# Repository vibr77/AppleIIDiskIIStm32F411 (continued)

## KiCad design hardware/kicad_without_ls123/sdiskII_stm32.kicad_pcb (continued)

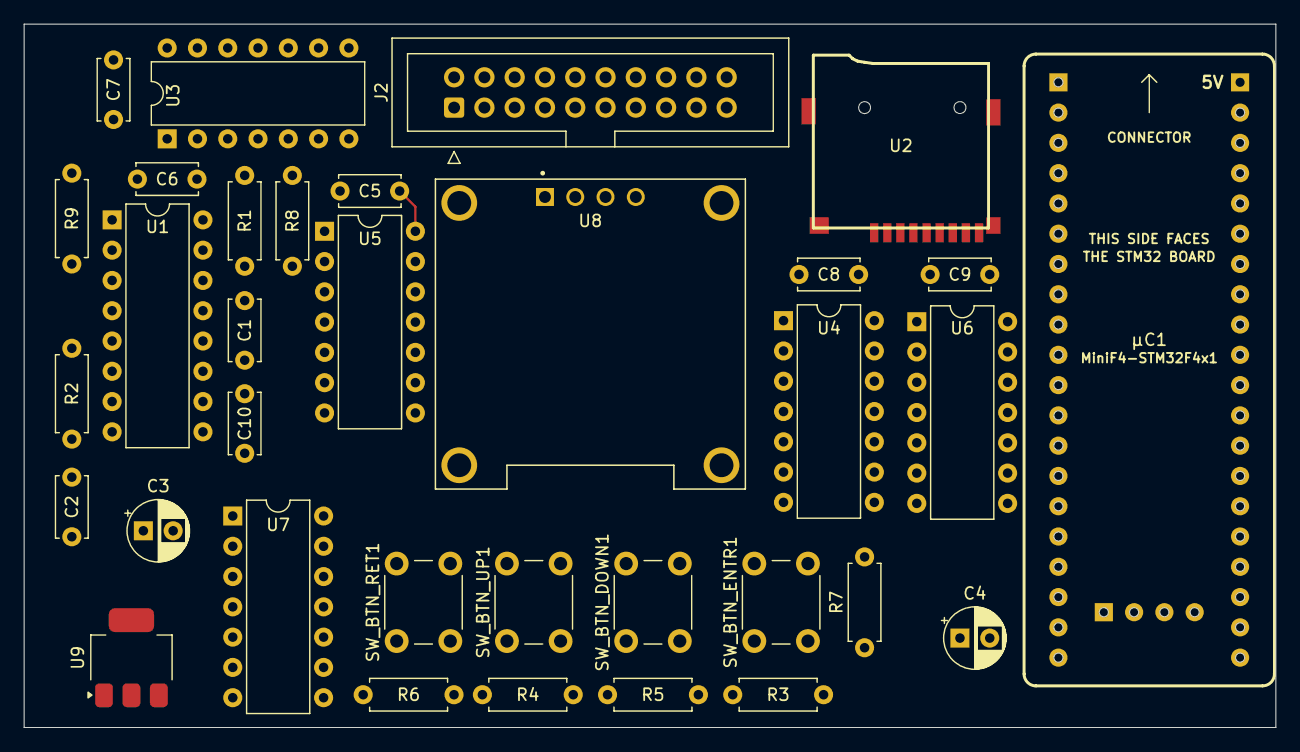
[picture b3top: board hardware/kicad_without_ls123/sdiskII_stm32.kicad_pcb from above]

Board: 2 copper layers, 105.0 x 59.0 mm, 34 parts (0 on the bottom side), 47 nets.

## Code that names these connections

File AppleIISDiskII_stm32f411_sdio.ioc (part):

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Mcu.Name=STM32F411C(C-E)Ux
Mcu.Package=UFQFPN48
Mcu.UserName=STM32F411CEUx
PA0-WKUP.GPIOParameters=GPIO_PuPd,GPIO_Label,GPIO_ModeDefaultEXTI
PA0-WKUP.GPIO_Label=STEP0
PA0-WKUP.GPIO_ModeDefaultEXTI=GPIO_MODE_IT_RISING_FALLING
PA0-WKUP.GPIO_PuPd=GPIO_PULLDOWN
PA0-WKUP.Signal=GPXTI0
PA1.GPIOParameters=GPIO_PuPd,GPIO_Label,GPIO_ModeDefaultEXTI
PA1.GPIO_Label=STEP1
PA1.GPIO_ModeDefaultEXTI=GPIO_MODE_IT_RISING_FALLING
PA1.GPIO_PuPd=GPIO_PULLDOWN
PA1.Signal=GPXTI1
PA10.GPIOParameters=GPIO_Speed,GPIO_Label
PA10.GPIO_Label=DEBUG
PA10.GPIO_Speed=GPIO_SPEED_FREQ_VERY_HIGH
PA10.Signal=GPIO_Output
PA11.GPIOParameters=GPIO_PuPd,GPIO_Label
PA11.GPIO_Label=_35DSK
PA11.GPIO_PuPd=GPIO_PULLDOWN
PA11.Signal=GPIO_Input
PA15.Mode=Asynchronous
PA15.Signal=USART1_TX
PA2.GPIOParameters=GPIO_PuPd,GPIO_Label,GPIO_ModeDefaultEXTI
PA2.GPIO_Label=STEP2
PA2.GPIO_ModeDefaultEXTI=GPIO_MODE_IT_RISING_FALLING
PA2.GPIO_PuPd=GPIO_PULLDOWN
PA2.Signal=GPXTI2
PA3.GPIOParameters=GPIO_PuPd,GPIO_Label,GPIO_ModeDefaultEXTI
PA3.GPIO_Label=STEP3
PA3.GPIO_ModeDefaultEXTI=GPIO_MODE_IT_RISING_FALLING
PA3.GPIO_PuPd=GPIO_PULLDOWN
PA3.Signal=GPXTI3
PA4.GPIOParameters=GPIO_PuPd,GPIO_Label,GPIO_ModeDefaultEXTI
PA4.GPIO_Label=DEVICE_ENABLE
PA4.GPIO_ModeDefaultEXTI=GPIO_MODE_IT_RISING_FALLING
PA4.GPIO_PuPd=GPIO_PULLUP
PA4.Signal=GPXTI4
PA5.Signal=S_TIM2_CH1_ETR
PA6.GPIOParameters=GPIO_PuPd
PA6.GPIO_PuPd=GPIO_PULLUP
PA6.Mode=SD_4_bits_Wide_bus
PA6.Signal=SDIO_CMD
PA7.GPIOParameters=GPIO_PuPd,GPIO_Label
PA7.GPIO_Label=WR_DATA
PA7.GPIO_PuPd=GPIO_PULLDOWN
PA7.Signal=GPIO_Input
PA8.GPIOParameters=GPIO_PuPd
PA8.GPIO_PuPd=GPIO_PULLUP
PA8.Mode=SD_4_bits_Wide_bus
PA8.Signal=SDIO_D1
PA9.GPIOParameters=GPIO_PuPd
PA9.GPIO_PuPd=GPIO_PULLUP
PA9.Mode=SD_4_bits_Wide_bus
PA9.Signal=SDIO_D2
PB0.GPIOParameters=GPIO_Speed,GPIO_PuPd,GPIO_Label
PB0.GPIO_Label=RD_DATA
PB0.GPIO_PuPd=GPIO_PULLDOWN
PB0.GPIO_Speed=GPIO_SPEED_FREQ_VERY_HIGH
PB0.Signal=GPIO_Output
PB1.Signal=S_TIM3_CH4
PB10.Signal=S_TIM2_CH3
PB12.GPIOParameters=GPIO_PuPd,GPIO_Label
PB12.GPIO_Label=BTN_RET
PB12.GPIO_PuPd=GPIO_PULLDOWN
PB12.Signal=GPXTI12
PB13.GPIOParameters=GPIO_PuPd,GPIO_Label
PB13.GPIO_Label=SD_EJECT
PB13.GPIO_PuPd=GPIO_PULLUP
PB13.Signal=GPIO_Input
PB14.Mode=PWM Generation2 CH2N
PB14.Signal=TIM1_CH2N
PB15.Mode=SD_4_bits_Wide_bus
PB15.Signal=SDIO_CK
PB2.GPIOParameters=GPIO_Label
PB2.GPIO_Label=WR_PROTECT
PB2.Signal=GPIO_Output
PB3.Mode=Asynchronous
PB3.Signal=USART1_RX
PB4.GPIOParameters=GPIO_PuPd
PB4.GPIO_PuPd=GPIO_PULLUP
PB4.Mode=SD_4_bits_Wide_bus
PB4.Signal=SDIO_D0
PB5.GPIOParameters=GPIO_PuPd
PB5.GPIO_PuPd=GPIO_PULLUP
PB5.Mode=SD_4_bits_Wide_bus
PB5.Signal=SDIO_D3
PB6.Mode=I2C
PB6.Signal=I2C1_SCL
PB7.Mode=I2C
PB7.Signal=I2C1_SDA
PB8.GPIOParameters=GPIO_Label,GPIO_ModeDefaultEXTI
PB8.GPIO_Label=SELECT
PB8.GPIO_ModeDefaultEXTI=GPIO_MODE_IT_RISING_FALLING
PB8.Signal=GPXTI8
PB9.GPIOParameters=GPIO_PuPd,GPIO_Label,GPIO_ModeDefaultEXTI
PB9.GPIO_Label=WR_REQ
PB9.GPIO_ModeDefaultEXTI=GPIO_MODE_IT_RISING_FALLING
PB9.GPIO_PuPd=GPIO_PULLUP
PB9.Signal=GPXTI9
PC13-ANTI_TAMP.GPIOParameters=GPIO_PuPd,GPIO_Label
PC13-ANTI_TAMP.GPIO_Label=BTN_DOWN
PC13-ANTI_TAMP.GPIO_PuPd=GPIO_PULLDOWN
PC13-ANTI_TAMP.Signal=GPXTI13
PC14-OSC32_IN.GPIOParameters=GPIO_PuPd,GPIO_Label
PC14-OSC32_IN.GPIO_Label=BTN_UP
PC14-OSC32_IN.GPIO_PuPd=GPIO_PULLDOWN
PC14-OSC32_IN.Signal=GPXTI14
PC15-OSC32_OUT.GPIOParameters=GPIO_PuPd,GPIO_Label
PC15-OSC32_OUT.GPIO_Label=BTN_ENTR
PC15-OSC32_OUT.GPIO_PuPd=GPIO_PULLDOWN
PC15-OSC32_OUT.Signal=GPXTI15
PH0\ -\ OSC_IN.Mode=HSE-External-Oscillator
PH0\ -\ OSC_IN.Signal=RCC_OSC_IN
PH1\ -\ OSC_OUT.Mode=HSE-External-Oscillator
PH1\ -\ OSC_OUT.Signal=RCC_OSC_OUT
RCC.HSE_VALUE=25000000
RCC.SYSCLKFreq_VALUE=96000000
RCC.SYSCLKSource=RCC_SYSCLKSOURCE_PLLCLK
board=custom

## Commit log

2024-08-27 Initial comit
    Initial commit
2024-08-28 disable and IRQ changes
2024-08-28 working read
2024-08-29 all images working
2024-09-01 Code cleaning, warning suppress, casting
2024-09-02 code cleanup
2024-09-24 Working on UI
2024-09-24 work on UI
2024-10-09 new realease with gerber
2024-10-16 first PCB version
2024-10-16 BTN Pin definition update
2024-10-16 stcubemx pin def update (btn)
2024-10-16 clean up
2024-10-17 readme update
2024-10-17 cleanup
2024-10-17 readme
2024-10-18 photo readme
2024-10-18 photo
2024-10-22 change makefile to use bootloader, CPU Freq, align TIMER config
2024-10-22 pin config & uart
2024-10-24 beaming process update, main menu first implementation
2024-10-27 v0.64
2024-10-27 v0.65
2024-10-28 v0.66 NIC Driver Fix
2024-10-28 v0.66 NIC Fix
2024-10-28 v0.67 Fix Startup / Display Reset ...
2024-10-29 button & function inversion
2024-10-29 button definition
2024-10-29 driver work
2024-10-30 v0.68 Fix WOZ1.0 Read
2024-10-31 working on dsk driver
2024-10-31 adding PO support as well
2024-10-31 fixing some type issues
2024-10-31 rotation of ico, new ico, Ux work
2024-10-31 changing clock div for sdio
2024-11-01 v0.70: favorites + display
2024-11-01 addtofavorite
2024-11-01 v0.70: bug fixing
2024-11-01 remove parson.c
2024-11-02 feat: config menu screen
2024-11-02 fix: default configFile initialization if not exist, display adjust
2024-11-02 !refactor: display function
2024-11-02 v0.71
2024-11-04 fix: directory with name of 1 char not read by the emulator
2024-11-05 v0.72: ImageMenu + Fix
2024-11-07 before_sound processing
2024-11-07 feat: buzzer timer
2024-11-07 board rev20
2024-11-07 board rev2
2024-11-09 v0.73: code refactoring + buzzer sound
2024-11-09 v0.73: fixing config size
2024-11-15 v0.74 - Not running
2024-11-15 v0.75: working
2024-11-17 v0.76
2024-11-21 fix: v0.76 woz protection (all images working)
2024-11-21 hardware rev2 (including buzzer)
2024-11-21 kicad v2
2024-11-21 Remove .DS_Store from everywhere
2024-11-21 .DS_Store Ignore
2024-11-22 upd: documentation
2024-11-22 fix: DSK/NIC Reading
2024-11-23 spiradisc fix
2024-11-23 v0.78.1
2024-11-26 working on write
2024-11-27 working wrdata byte stream
2024-11-27 optimising woz writing process
2024-11-28 write process part 2
2024-11-28 Writing works using LockSmtih 6.0
2024-12-22 v0.79 Smartport HD working
2024-12-22 v0.79 Smartport write testing
2024-12-23 v0.79 smartport #2
2024-12-23 remove of archive
2024-12-24 3D print case
2024-12-24 bambulab prj
2024-12-26 smartport fix
2024-12-26 case
2024-12-26 fix ARM Toolchain 14.2
2024-12-26 middleware fix
2024-12-26 rev4 (aesthetic change)
2025-01-04 v0.79.1
2025-01-20 write part, almost there
2025-01-23 write
2025-01-24 write woz change
2025-01-24 0.79.2 release
2025-01-24 0.79.2
2025-01-27 v0.79.3 Smartport HD, DIsk II, Case v3 display refactoring
2025-01-30 display menu fix
2025-02-02 v0.79.6 Fixing Smartport IIGS
2025-02-06 v0.81 Smartport write
2025-02-09 Contributed hardware
2025-02-10 initial disk3.5 work
2025-02-20 Initial upload
    Rotary encoder support buggy
2025-02-21 RE update
2025-02-21 Make Filsystem fixed
2025-02-21 Reset on push all
    clearScreen fix
2025-02-22 display fix
2025-02-22 final v0.80.1
2025-02-23 work on v0.82
2025-02-23 merged v0.83
2025-02-26 v0.80.3 23.02.25 v0.80.3 + [All] Code cleaning, compilation warning cleaning + [Smartport] 2MG Extension checking fixed + [2MG] Fixing 2MG mount blockCount function + [Smartport] Fixing Missing Exten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
2025-02-27 26.02.25 v0.80.4 + [WOZ] Passing the wozardry verify & dump test for both 3.5 & 5.25 + [WOZ] Manage CRC32 + [WOZ] Adding Blank woz file creation for 3.5 + [WOZ] Adding Blank woz file creation for 5.25
2025-02-27 + [WOZ] Correcting head / sector / region calculation + [FS] Adding "." item on every location to add future access to option
2025-03-10 work in progress
2025-03-11 smartport fs hook
2025-03-12 work on disk35 emulation
2025-03-12 added configuration for select & 35DSK line
2025-03-13 dsk write part 1
2025-03-14 fs deadlock fix
    fixing some deadlock on fs
2025-03-16 Core/Inc/display.h: fix path typos
2025-03-19 beta v0.85
2025-03-20 code clean up
2025-03-20 v0.80.5 Beta
2025-03-20 add PO writing support
2025-03-21 v0.80.5.b2
2025-03-21 write partially working
2025-03-21 v0.80.5.c
2025-03-21 v0.80.5.d
2025-03-21 v0.80.5.e init DOS working
2025-03-21 add missing IRQ (Select)
2025-03-21 fixing Cross track sync with new reading proc
2025-03-22 v0.80.5d Smartport Nav Fix
2025-03-22 main menu
2025-03-22 workspc
2025-03-22 fixing boot up and write protect on start up IIc & IIGS
2025-03-22 IIGS & IIC Fix
2025-03-22 fixing checksum calculation on write
2025-03-23 0.85b fix
2025-03-24 fixing makefs
2025-03-24 Remove deadlock on smartport
2025-03-24 wip v0.81
2025-03-25 0.81 wip2
2025-03-25 v0.81 wip3
2025-03-25 wip4
2025-03-26 A2F 0.86 fix
2025-03-26 uf2 build update
2025-03-26 rename u2f files
2025-03-26 v0.81 wip5
2025-03-26 v0.80.7 wip5
2025-03-27 v0.81 wip6
2025-03-29 new A2F build und further adjustments
2025-04-04 v0.80.9
2025-04-06 display fix and 0.80.9 A2F build
    The top line of the T of the Track: was missing
2025-04-07 adding SDCARD getState for diskii & smartport
2025-04-11 v0.80.11
2025-04-14 test on write
2025-04-23 A2F smartport fix
2025-05-07 pcb small change v5
2025-05-19 v0.80.12 beta
2025-05-19 PCB Rev6
2025-05-19 define PWR A12
2025-05-20 v0.80.13 beta #1
2025-05-21 v0.80.13 rel
2025-05-21 mxproject
2025-05-21 A2F build fix
2025-05-21 A2F typo fix
2025-05-21 A2F 0.80.13 build
2025-07-14 fixing Smartport on IIe II+ Rev6 Hardware
2025-07-14 v0.80.14
2025-07-20 smartloader beta #1
2025-07-23 smartloader work #2
2025-07-23 v0.80.15 #1
2025-07-23 v0.80.15c
2025-07-28 smartloader case comp
2025-08-03 add emulation type Smartloader
2025-08-11 Board rev7 beta
2025-08-12 v0.80.17 Alpha
2025-08-12 v0.80.17 Alpha 2 code relagn with STCube MX
2025-08-12 v0.80.17 Alpha 3
2025-08-12 Board Rev7 beta 2 # Add bypass pads
2025-08-18 0.80.17 beta 4
2025-08-19 0.80.18 beta 1, fatfs0.16, screensaver, stm32 firmware 1.28.2
2025-08-19 changing splash,adding animation
2025-08-19 PCB Board v7 Adjust + 3D Print Case
2025-08-19 realign IOC MX with Code
2025-08-20 Board Rev7 to test production
2025-08-22 v0.80 beta 4
2025-08-22 beta 5
2025-08-22 Beta 6
2025-08-23 v0.80.18 beta 7
2025-08-23 beta 8
2025-08-23 v0.80.18 beta 9 - Add Fav to Smartloader
2025-08-24 v0.80.18 Beta 10 Integration of Smartloader in firmware with Emulation type
2025-08-24 v0.80.18 beta 11 Mod of Makefile
2025-10-03 v0.80.20.4
2025-10-04 v0.80.21 Fixing IIe IIc Smartport
2025-10-10 v0.80.22
2025-10-11 v0.80.23 wip #1
2025-10-19 v0.80.24
2025-10-21 IIc boot issue on Smartport (Bootloader issue?)
2025-10-21 Fixing Checksum on IIc & IIe Message without trailing C8 !!!!
2025-10-21 test
2025-10-27 v0.80.27 #1
2025-10-27 v0.80.27 #2
2025-10-27 v0.80.28 fixing TIM5
2025-10-30 v0.80.29 WIP #1
2025-10-31 v0.80.29 WIP #2
2025-10-31 v0.80.29
2025-11-02 v0.80.29 WIP (WR not working)
2025-11-10 v0.80.29 WIP #3 Disk Write Error speed
2025-11-10 v0.80.29 WIP #4
2025-11-15 WIP WR #5
2025-11-16 Yellowstone WIP #1
2025-11-16 Yellowstone WIP #2
2025-11-16 IIGS IIE YS WR DISKII OK (DSK,WOZ)
2025-11-16 fix buzzer when writing
2025-11-16 Display WR during write process
2025-11-16 YS WIP
2025-11-18 + Add Marquee Management
2025-11-18 YellowStone working !
2025-11-19 v0.31 WIP #1
2025-11-19 YS & DISKII WR OK
2025-11-20 screen marquee fix
2025-11-20 smartport sizefix
2025-11-20 bootloader +makefile
2025-11-20 Smartport IIGS bootup timing fix
2025-11-21 v0.32 Smartloaer
2025-11-22 v0.80.33
2026-02-05 fixing deadlock on sdcard
2026-02-05 v0.34
